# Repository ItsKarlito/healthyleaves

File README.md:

# ELEC/COEN 390 Engineering Team Design Project

**HealthyLeaves** is consumer electronics device used to monitor the vitals of any plant. Using a combination of powerful hardware and software, HealthyLeaves guarantees healthier and longer lasting house plants.

## Contributors
Daniel Savin (ELEC)  
Jun Young David Kim (ELEC)  
Karl Noory (ELEC)  
Thomas Tran (COEN)  
Vily Badea (COEN)  

## Supervision
Bipin Patel  
Dr. Wahab Hamou Lhadj  

## Technology Stack
Android Studio IDE  
Arduino C/C++  
Arduino IDE  
ESP32 Microcontroller  
Firebase  
Git  
Java  
KiCAD  
LDR Light Sensor  
SEN0193 Capcitive Moisture Sensor  
TensorFlow  
TMP36 Temperature Sensor  

## App Installation Guide
### Steps
1. Clone project repository.
1. Open PlantMonitor Android project in .software/PlantMonitor.
1. Build Gradle of PlantMonitor Android app.
1. Run PlantMonitor Android app.
1. Open PlantIdentier Android project in .software/PlantIdentifier.
1. Build Gradle of PlantIdentifier Android app.
1. Run PlantIdentifier Android app.
1. You can now access the application called "Healthy Leaves".

### Notes
Make sure the filepath for the SDK manager points to your own directory.  
The build.gradle file will need to specify the version of your own Android Studio version.  
A device is not requiered to run the app.  
To pair the device to our demo device on Karl's plant, enter the device code as "-MLuKU9iZdUl5zLGsuPz".  

## Microcontroller Setup Guide
### Steps
1. Clone project repository.
1. Download and install the [FirebaseESP32](https://www.arduino.cc/reference/en/libraries/firebase-esp32-client/) client library. Import the library into the [Arduino IDE](https://www.arduino.cc/en/software).
1. Open the HealthyLeaves Arduino project located at engineering-team-design-project/hardware/sparkfunESP32/HealthyLeaves/
1. Edit sketch with proper WiFi and Firebase credentials.
1. Attach the HealthyLeaves sensor shield to the SparkFun ESP32 Thing.
1. Connect the SparkFun ESP32 Thing microcontroller to your computer via USB port. Follow the steps [here](https://learn.sparkfun.com/tutorials/esp32-thing-hookup-guide) if the Arduino IDE does not recognise the SparkFun ESP32 Thing.
1. Compile and upload the sketch to the SparkFun ESP32 Thing.
1. Place the end of the moisture sensor located on the HealthyLeaves sensor shield into the plant you want to monitor.

### Notes
A device is not requiered to run the app.  
To pair the device to our demo device on Karl's plant, enter the device code as "-MLuKU9iZdUl5zLGsuPz" in the HealthyLeaves Arduino sketch.  

## Pictures and Screenshots
### Android Application

### Hardware

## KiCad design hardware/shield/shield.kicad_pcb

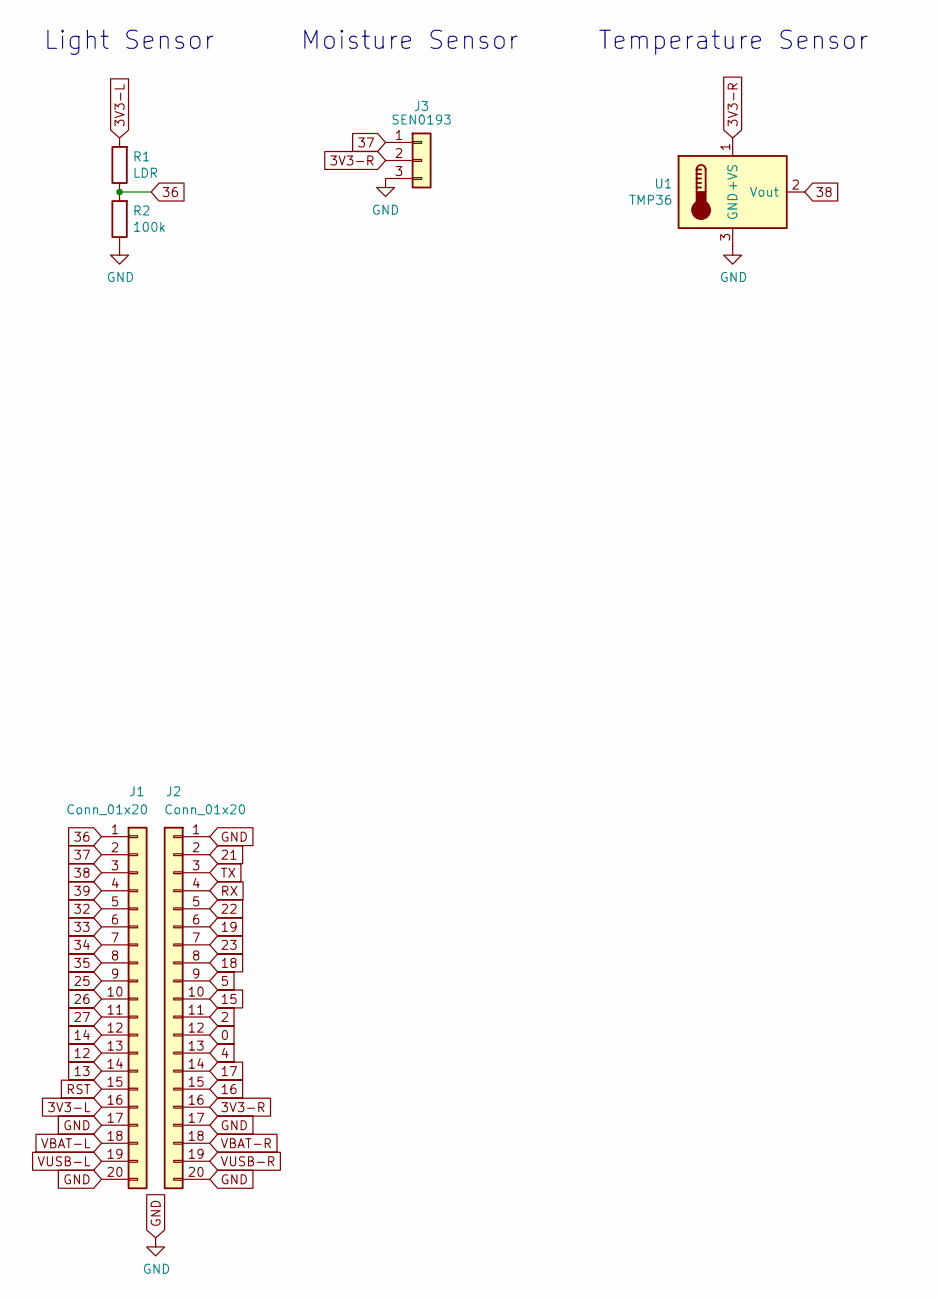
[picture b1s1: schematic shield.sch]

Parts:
J1, J2: Conn_01x20; PinHeader_1x20_P2.54mm_Vertical
J3: SEN0193; PinHeader_1x03_P2.54mm_Vertical
R1: LDR; R_LDR_4.9x4.2mm_P2.54mm_Vertical
R2: 100k; R_Axial_DIN0207_L6.3mm_D2.5mm_P10.16mm_Horizontal
U1: TMP36; TO-92L_Inline

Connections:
0: J2.12
2: J2.11
3V3-L: J1.16, R1.2
3V3-R: J2.16, J3.2, U1.1 (+VS)
4: J2.13
5: J2.9
12: J1.13
13: J1.14
14: J1.12
15: J2.10
16: J2.15
17: J2.14
18: J2.8
19: J2.6
21: J2.2
22: J2.5
23: J2.7
25: J1.9
26: J1.10
27: J1.11
32: J1.5
33: J1.6
34: J1.7
35: J1.8
36: J1.1, R1.1, R2.2
37: J1.2, J3.1
38: J1.3, U1.2 (Vout)
39: J1.4
GND: J1.17, J1.20, J2.1, J2.17, J2.20, J3.3, R2.1, U1.3 (GND)
RST: J1.15
RX: J2.4
TX: J2.3
VBAT-L: J1.18
VBAT-R: J2.18
VUSB-L: J1.19
VUSB-R: J2.19

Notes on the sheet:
Light Sensor
Temperature Sensor
Moisture Sensor

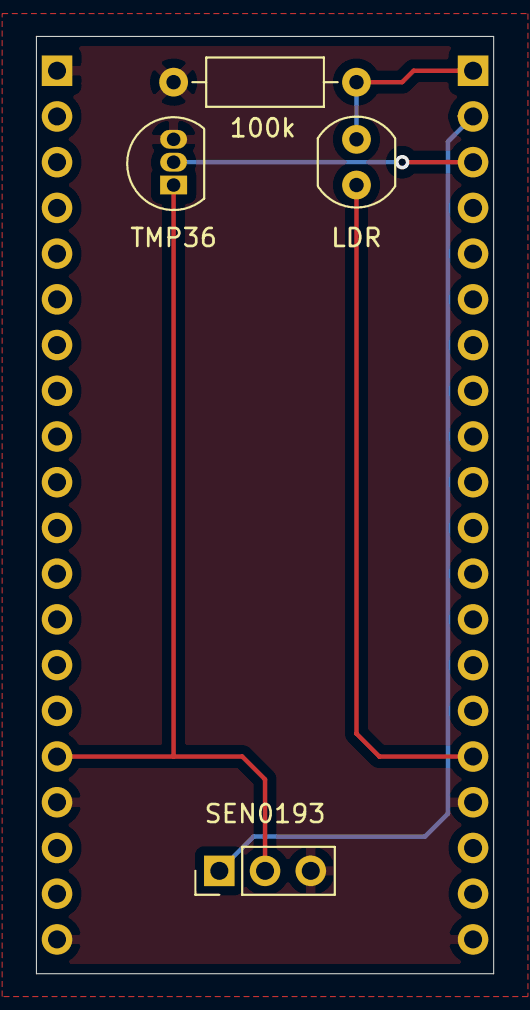
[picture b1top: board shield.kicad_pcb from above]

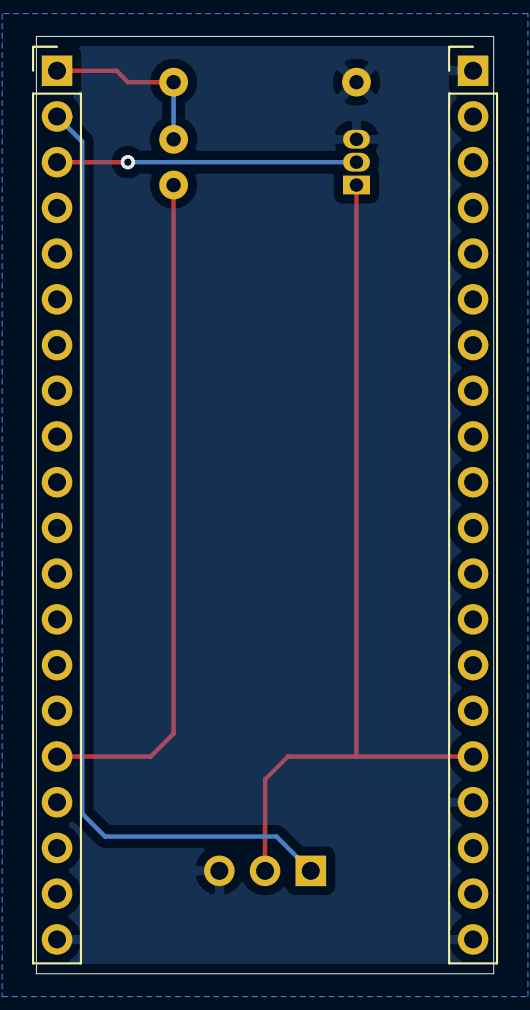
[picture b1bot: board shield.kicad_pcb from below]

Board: 2 copper layers, 25.4 x 52.1 mm, 6 parts (2 on the bottom side), 6 nets.

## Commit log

2020-10-25 npm init
2020-10-26 link established between pi and firebase
2020-10-29 for iteration of basic plant monitor UI
2020-10-30 link established between esp32 and firebase
2020-10-31 firebase connection firebase messaging service profile activity login profile
2020-10-31 firebase connection, push notification, profile creation and login
2020-11-01 merged the plant database firebase on android application project into the team's branch with authentication and local database
2020-11-03 getEpochTime, writeToDatabase, userPlantId
2020-11-06 added getTemperature, getLightIntensity, block-diagram.xml
2020-11-06 initialized kicad project, sparkfunESP32 shield
2020-11-06 added sparkfunESP32 schematic
2020-11-06 added sparkfunESP32 pinout
2020-11-06 added ESP32 datasheet
2020-11-06 added .gitignore
2020-11-06 sparkfunESP32 shield pcb, temperature and light sensors
2020-11-07 refactored the java code for names that explain better their usage and folders that seperate the application into the main features and activities
2020-11-09 refactored the code, added the edit plant catalog feature including the activity, the button that goes to that activity with the adequate intent and the functionalities to the firebase database, fixe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
2020-11-09 fixed a bug with the add plant button in plant catalog and started implementation of OwnsA relationship creation
2020-11-09 cleaned build code, refactored some code, and implemented the OwnsA relationship with its implied features
2020-11-10 added logout button and fixed .gitignore file
2020-11-10 Revert "Vily notifications"
2020-11-10 Revert "added logout button and fixed .gitignore file"
2020-11-10 added logout feature
2020-11-10 cleaned build
2020-11-10 parent/child activity hierarchy
2020-11-11 logout button
2020-11-11 added in .gitignore local.properties
2020-11-11 OwnsA relationship can be created properly from the catalog page using the add button. User plants can be created by saving the plantID and userID and a name as a tuple
2020-11-11 added Arduino code for moisture sensor read (no Firebase)
2020-11-11 feature of displaying all user specific plants in a recycler view has been implemented but there's a bug that makes it only show new relationships, will check on it tomorrow
2020-11-12 fixed userPlantsList display bug and feature is completed. A prop page of the plant profile has been implemented too
2020-11-12 userPlantId updated
2020-11-14 Refactored hardware code and included moisture
2020-11-15 triggering firebase functions
2020-11-15 refactoring: - var number diminished - vars are moved to their function respective scopes - getTemperature() formula changed - added comments
2020-11-15 changing .gitignore file
2020-11-15 fixed all bugs found in testing from srpint 1
2020-11-15 removed .gitignore
2020-11-15 removed unecessary files
2020-11-15 added proper software/PlantMonitor/.gitignore
2020-11-15 updated software/PlantMonitor/.gitignore
2020-11-16 deleted software/PlantMonitor/.idea/codeStyles/Project.xml
2020-11-16 stashing
2020-11-16 rewrote the xml layout files for the adapters
2020-11-16 added shield .gitignore
2020-11-16 app has been repaired and some UI was conformed
2020-11-16 updated shield for sparkfunESP32
2020-11-16 refactored and renamed app
2020-11-16 added external-hardware-3d.xml
2020-11-16 attempt to read measured data and display it
2020-11-16 just to be sure
2020-11-17 updated pcb connector, added logo and version number
2020-11-19 added firebase backup
2020-11-24 data graphing feature with listview for previous data
2020-11-30 adjustments to data ranges
2020-11-30 fixed bug of plantProfileActivity fetching too many data points
2020-12-01 updated userPlantId and database backup
2020-12-01 fixed problem with clumped x values in graph
2020-12-01 fixed multiple bugs, improved UI, actions recommendations feature, arduino pairing both ways possible
2020-12-01 fixed a minor bug in a textview
2020-12-01 verify values of written data to firebase and display relevant notification
2020-12-01 fixed type associated to right userPlant bug
2020-12-01 updated UI of graph and details activities
2020-12-01 can't access data if not the specific userPlant
2020-12-01 fixed issue with graph not showing all data
2020-12-01 added shouldNotify boolean to check if notification should be sent
2020-12-02 changed minimum and high values
2020-12-02 plant identifier feature completed, fixed bugs, improved UI
2020-12-02 Revert "Thomas object detection"
2020-12-02 changed naming of plant identifier app
2020-12-02 changed naming
2020-12-02 updated timing, userPlantID, and database backup
2020-12-02 renamed file
2020-12-02 notification changes to sprint3
2020-12-02 notif compare values
2020-12-02 cloud functions changes
2020-12-02 changed priority to high in index.ts and changed sendToTopic
2020-12-02 fixed light details graph bug that made app crash
2020-12-02 just to be safe
2020-12-02 graphs now work and update real time
2020-12-02 improved graph visuals
2020-12-02 light graph changes copied to moisture and temperature graph
2020-12-02 added screenshots of the app
2021-01-11 added pictures of hardware
2021-01-11 renamed android app screenshot files
